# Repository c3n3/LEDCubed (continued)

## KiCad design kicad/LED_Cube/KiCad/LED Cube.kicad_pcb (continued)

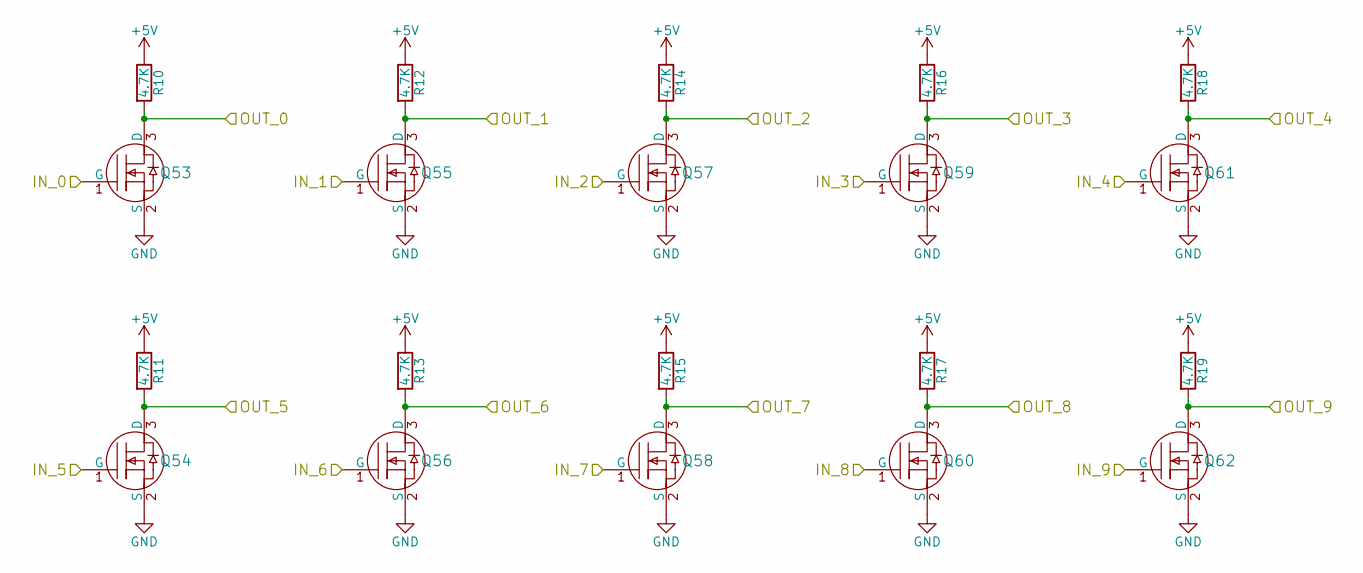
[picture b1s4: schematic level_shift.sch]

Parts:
Q53, Q54, Q55, Q56, Q57, Q58, Q59, Q60, Q61, Q62: N-Channel_MOSFET; SOT-23
R10, R11, R12, R13, R14, R15, R16, R17, R18, R19: 4.7K; R_0805_HandSoldering

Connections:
+5V: R10.1, R11.1, R12.1, R13.1, R14.1, R15.1, R16.1, R17.1, R18.1, R19.1; also elsewhere on the board
/Level Shift/IN_0: Q53.1 (G); also elsewhere on the board
/Level Shift/IN_1: Q55.1 (G); also elsewhere on the board
/Level Shift/IN_2: Q57.1 (G); also elsewhere on the board
/Level Shift/IN_3: Q59.1 (G); also elsewhere on the board
/Level Shift/IN_4: Q61.1 (G); also elsewhere on the board
/Level Shift/IN_5: Q54.1 (G); also elsewhere on the board
/Level Shift/IN_6: Q56.1 (G); also elsewhere on the board
/Level Shift/IN_7: Q58.1 (G); also elsewhere on the board
/Level Shift/IN_8: Q60.1 (G); also elsewhere on the board
/Level Shift/IN_9: Q62.1 (G); also elsewhere on the board
/Level Shift/OUT_0: Q53.3 (D), R10.2; also elsewhere on the board
/Level Shift/OUT_1: Q55.3 (D), R12.2; also elsewhere on the board
/Level Shift/OUT_2: Q57.3 (D), R14.2; also elsewhere on the board
/Level Shift/OUT_3: Q59.3 (D), R16.2; also elsewhere on the board
/MOSFET_TREE/C_B: Q62.3 (D), R19.2; also elsewhere on the board
/MOSFET_TREE/C_G: Q60.3 (D), R17.2; also elsewhere on the board
/MOSFET_TREE/C_R: Q58.3 (D), R15.2; also elsewhere on the board
/MOSFET_TREE/L_0: Q61.3 (D), R18.2; also elsewhere on the board
/MOSFET_TREE/L_1: Q54.3 (D), R11.2; also elsewhere on the board
/MOSFET_TREE/L_2: Q56.3 (D), R13.2; also elsewhere on the board
GND: Q53.2 (S), Q54.2 (S), Q55.2 (S), Q56.2 (S), Q57.2 (S), Q58.2 (S), Q59.2 (S), Q60.2 (S), Q61.2 (S), Q62.2 (S); also elsewhere on the board

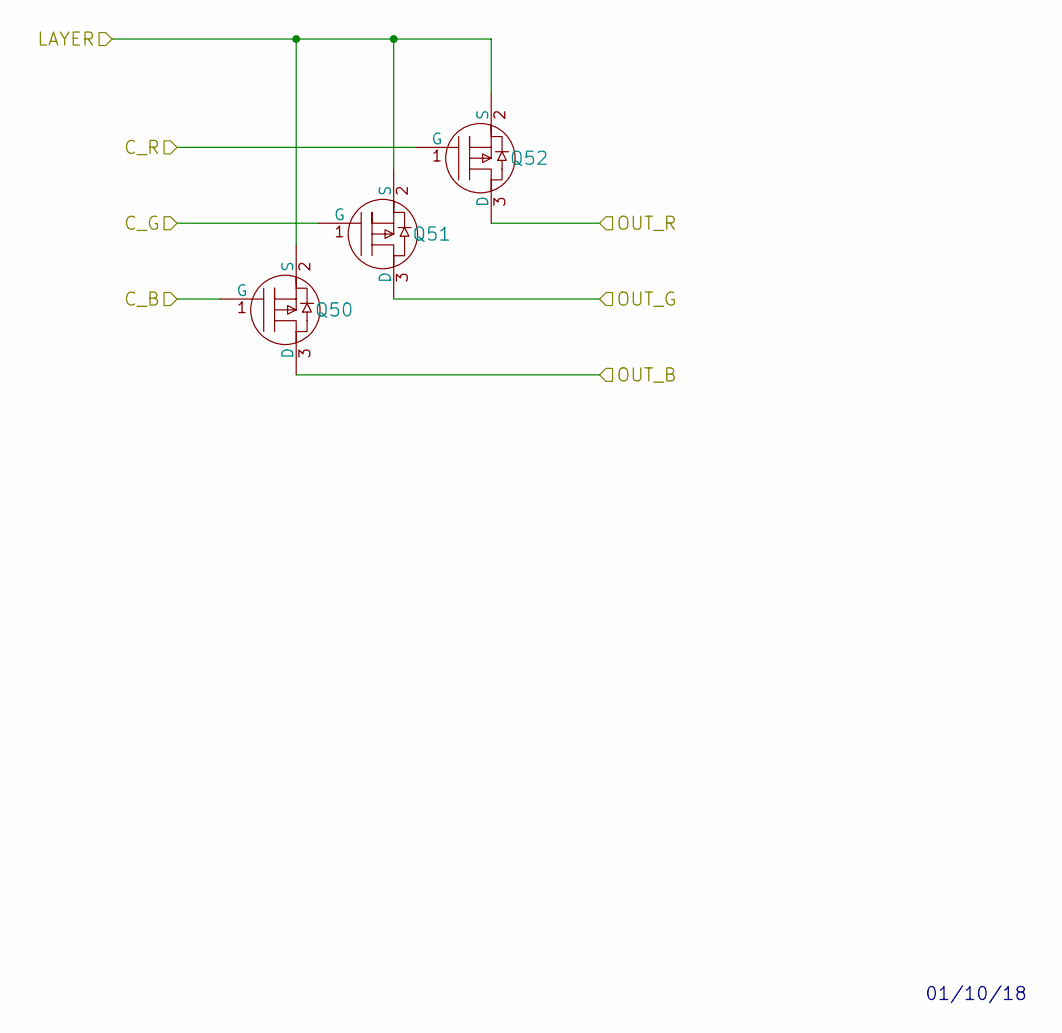
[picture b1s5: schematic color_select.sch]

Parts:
Q17, Q18, Q19: P-Channel_MOSFET; SOT-23

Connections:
/MOSFET_TREE/C_B: Q17.1 (G); also elsewhere on the board
/MOSFET_TREE/C_G: Q18.1 (G); also elsewhere on the board
/MOSFET_TREE/C_R: Q19.1 (G); also elsewhere on the board
/MOSFET_TREE/Color_Select_00/LAYER: Q17.2 (S), Q18.2 (S), Q19.2 (S); also elsewhere on the board
/MOSFET_TREE/L_00_B: Q17.3 (D); also elsewhere on the board
/MOSFET_TREE/L_00_G: Q18.3 (D); also elsewhere on the board
/MOSFET_TREE/L_00_R: Q19.3 (D); also elsewhere on the board

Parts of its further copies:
Q20, Q21, Q22, Q23, Q24, Q25, Q26, Q27, Q28, Q29, Q30, Q31, Q32, Q33, Q34, Q35, Q36, Q37, Q38, Q39, Q40, Q41, Q42, Q43, Q44, Q45, Q46, Q47, Q48, Q49, Q50, Q51, Q52: P-Channel_MOSFET; SOT-23

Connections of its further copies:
/MOSFET_TREE/C_B: Q20.1 (G), Q23.1 (G), Q26.1 (G), Q29.1 (G), Q32.1 (G), Q35.1 (G), Q38.1 (G), Q41.1 (G), Q44.1 (G), Q47.1 (G), Q50.1 (G); also elsewhere on the board
/MOSFET_TREE/C_G: Q21.1 (G), Q24.1 (G), Q27.1 (G), Q30.1 (G), Q33.1 (G), Q36.1 (G), Q39.1 (G), Q42.1 (G), Q45.1 (G), Q48.1 (G), Q51.1 (G); also elsewhere on the board
/MOSFET_TREE/C_R: Q22.1 (G), Q25.1 (G), Q28.1 (G), Q31.1 (G), Q34.1 (G), Q37.1 (G), Q40.1 (G), Q43.1 (G), Q46.1 (G), Q49.1 (G), Q52.1 (G); also elsewhere on the board
/MOSFET_TREE/Color_Select_01/LAYER: Q20.2 (S), Q21.2 (S), Q22.2 (S); also elsewhere on the board
/MOSFET_TREE/Color_Select_02/LAYER: Q23.2 (S), Q24.2 (S), Q25.2 (S); also elsewhere on the board
/MOSFET_TREE/Color_Select_03/LAYER: Q26.2 (S), Q27.2 (S), Q28.2 (S); also elsewhere on the board
/MOSFET_TREE/Color_Select_04/LAYER: Q29.2 (S), Q30.2 (S), Q31.2 (S); also elsewhere on the board
/MOSFET_TREE/Color_Select_05/LAYER: Q32.2 (S), Q33.2 (S), Q34.2 (S); also elsewhere on the board
/MOSFET_TREE/Color_Select_06/LAYER: Q35.2 (S), Q36.2 (S), Q37.2 (S); also elsewhere on the board
/MOSFET_TREE/Color_Select_07/LAYER: Q38.2 (S), Q39.2 (S), Q40.2 (S); also elsewhere on the board
/MOSFET_TREE/Color_Select_08/LAYER: Q41.2 (S), Q42.2 (S), Q43.2 (S); also elsewhere on the board
/MOSFET_TREE/Color_Select_09/LAYER: Q44.2 (S), Q45.2 (S), Q46.2 (S); also elsewhere on the board
/MOSFET_TREE/Color_Select_10/LAYER: Q47.2 (S), Q48.2 (S), Q49.2 (S); also elsewhere on the board
/MOSFET_TREE/Color_Select_11/LAYER: Q50.2 (S), Q51.2 (S), Q52.2 (S); also elsewhere on the board
/MOSFET_TREE/L_01_B: Q20.3 (D); also elsewhere on the board
/MOSFET_TREE/L_01_G: Q21.3 (D); also elsewhere on the board
/MOSFET_TREE/L_01_R: Q22.3 (D); also elsewhere on the board
/MOSFET_TREE/L_02_B: Q23.3 (D); also elsewhere on the board
/MOSFET_TREE/L_02_G: Q24.3 (D); also elsewhere on the board
/MOSFET_TREE/L_02_R: Q25.3 (D); also elsewhere on the board
/MOSFET_TREE/L_03_B: Q26.3 (D); also elsewhere on the board
/MOSFET_TREE/L_03_G: Q27.3 (D); also elsewhere on the board
/MOSFET_TREE/L_03_R: Q28.3 (D); also elsewhere on the board
/MOSFET_TREE/L_04_B: Q29.3 (D); also elsewhere on the board
/MOSFET_TREE/L_04_G: Q30.3 (D); also elsewhere on the board
/MOSFET_TREE/L_04_R: Q31.3 (D); also elsewhere on the board
/MOSFET_TREE/L_05_B: Q32.3 (D); also elsewhere on the board
/MOSFET_TREE/L_05_G: Q33.3 (D); also elsewhere on the board
/MOSFET_TREE/L_05_R: Q34.3 (D); also elsewhere on the board
/MOSFET_TREE/L_06_B: Q35.3 (D); also elsewhere on the board
/MOSFET_TREE/L_06_G: Q36.3 (D); also elsewhere on the board
/MOSFET_TREE/L_06_R: Q37.3 (D); also elsewhere on the board
/MOSFET_TREE/L_07_B: Q38.3 (D); also elsewhere on the board
/MOSFET_TREE/L_07_G: Q39.3 (D); also elsewhere on the board
/MOSFET_TREE/L_07_R: Q40.3 (D); also elsewhere on the board
/MOSFET_TREE/L_08_B: Q41.3 (D); also elsewhere on the board
/MOSFET_TREE/L_08_G: Q42.3 (D); also elsewhere on the board
/MOSFET_TREE/L_08_R: Q43.3 (D); also elsewhere on the board
/MOSFET_TREE/L_09_B: Q44.3 (D); also elsewhere on the board
/MOSFET_TREE/L_09_G: Q45.3 (D); also elsewhere on the board
/MOSFET_TREE/L_09_R: Q46.3 (D); also elsewhere on the board
/MOSFET_TREE/L_10_B: Q47.3 (D); also elsewhere on the board
/MOSFET_TREE/L_10_G: Q48.3 (D); also elsewhere on the board
/MOSFET_TREE/L_10_R: Q49.3 (D); also elsewhere on the board
/MOSFET_TREE/L_11_B: Q50.3 (D); also elsewhere on the board
/MOSFET_TREE/L_11_G: Q51.3 (D); also elsewhere on the board
/MOSFET_TREE/L_11_R: Q52.3 (D); also elsewhere on the board

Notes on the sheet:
01/10/18

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
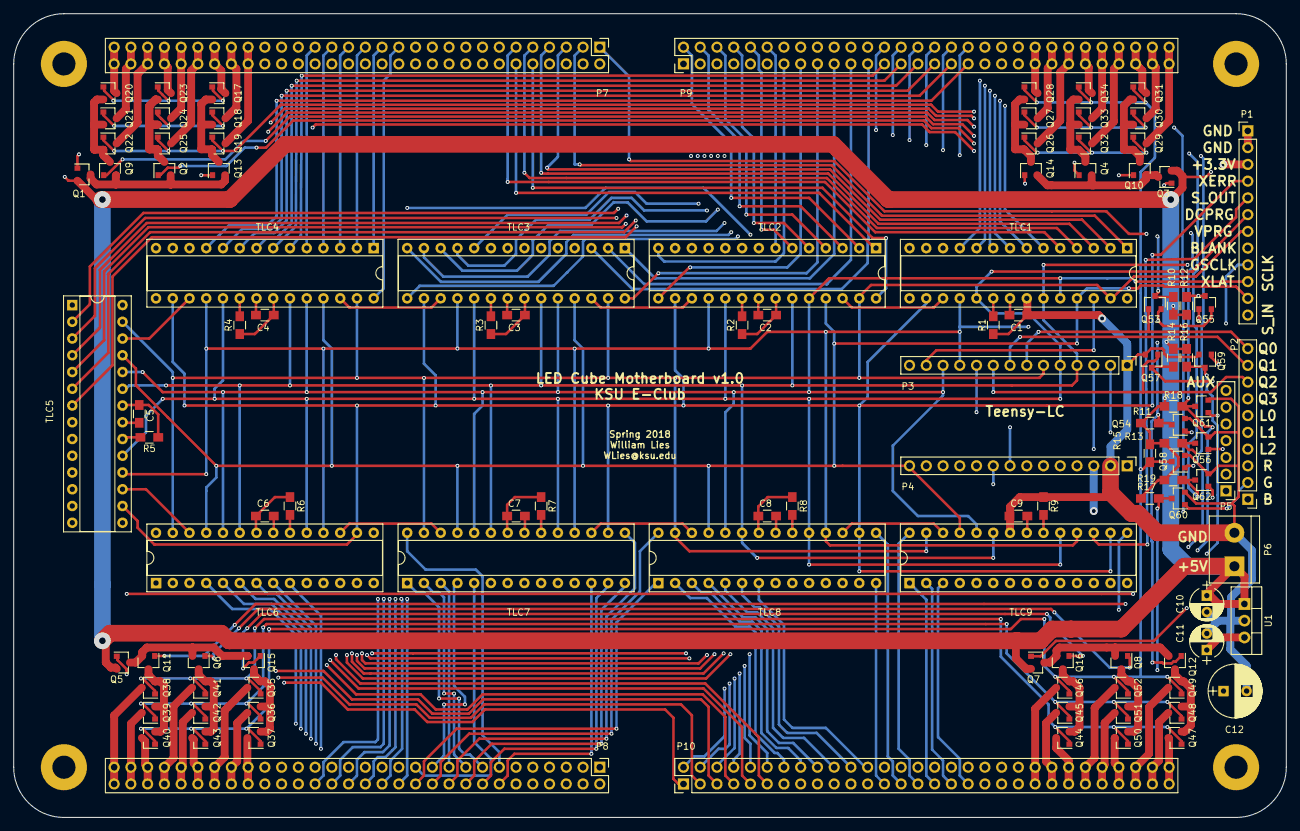
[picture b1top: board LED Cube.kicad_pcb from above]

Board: 4 copper layers, 193.0 x 121.9 mm, 113 parts (0 on the bottom side), 252 nets.

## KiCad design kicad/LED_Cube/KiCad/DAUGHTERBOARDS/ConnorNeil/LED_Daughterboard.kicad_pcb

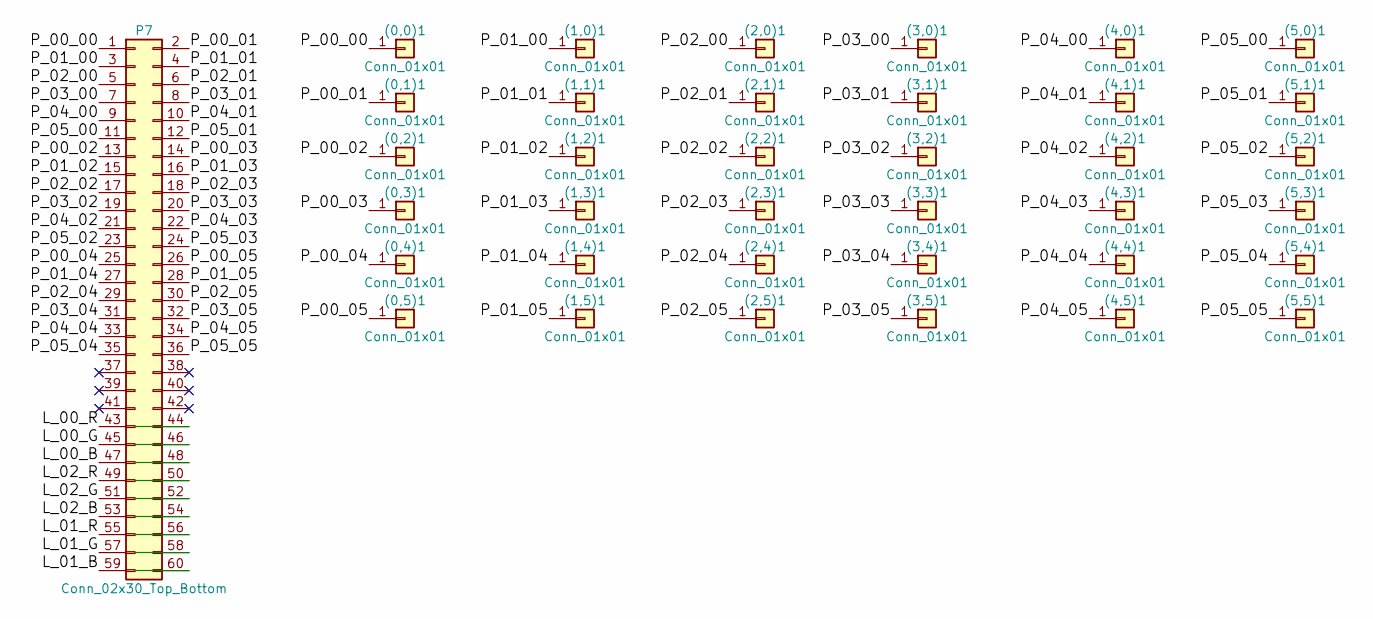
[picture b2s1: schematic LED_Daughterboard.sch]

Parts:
(0,0)1, (0,1)1, (0,2)1, (0,3)1, (0,4)1, (0,5)1, (1,0)1, (1,1)1, (1,2)1, (1,3)1, (1,4)1, (1,5)1, (2,0)1, (2,1)1, (2,2)1, (2,3)1, (2,4)1, (2,5)1, (3,0)1, (3,1)1, (3,2)1, (3,3)1, (3,4)1, (3,5)1, (4,0)1, (4,1)1, (4,2)1, (4,3)1, (4,4)1, (4,5)1, (5,0)1, (5,1)1, (5,2)1, (5,3)1, (5,4)1, (5,5)1: Conn_01x01; Pin_Header_Straight_1x01_Pitch2.54mm
P7: Conn_02x30_Top_Bottom; Pin_Header_Straight_2x30_Pitch2.54mm

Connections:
/L_00_B: P7.47
/L_00_G: P7.45
/L_00_R: P7.43
/L_01_B: P7.59
/L_01_G: P7.57
/L_01_R: P7.55
/L_02_B: P7.53
/L_02_G: P7.51
/L_02_R: P7.49
/P_00_00: (0,0)1.1, P7.1
/P_00_01: (0,1)1.1, P7.2
/P_00_02: (0,2)1.1, P7.13
/P_00_03: (0,3)1.1, P7.14
/P_00_04: (0,4)1.1, P7.25
/P_00_05: (0,5)1.1, P7.26
/P_01_00: (1,0)1.1, P7.3
/P_01_01: (1,1)1.1, P7.4
/P_01_02: (1,2)1.1, P7.15
/P_01_03: (1,3)1.1, P7.16
/P_01_04: (1,4)1.1, P7.27
/P_01_05: (1,5)1.1, P7.28
/P_02_00: (2,0)1.1, P7.5
/P_02_01: (2,1)1.1, P7.6
/P_02_02: (2,2)1.1, P7.17
/P_02_03: (2,3)1.1, P7.18
/P_02_04: (2,4)1.1, P7.29
/P_02_05: (2,5)1.1, P7.30
/P_03_00: (3,0)1.1, P7.7
/P_03_01: (3,1)1.1, P7.8
/P_03_02: (3,2)1.1, P7.19
/P_03_03: (3,3)1.1, P7.20
/P_03_04: (3,4)1.1, P7.31
/P_03_05: (3,5)1.1, P7.32
/P_04_00: (4,0)1.1, P7.9
/P_04_01: (4,1)1.1, P7.10
/P_04_02: (4,2)1.1, P7.21
/P_04_03: (4,3)1.1, P7.22
/P_04_04: (4,4)1.1, P7.33
/P_04_05: (4,5)1.1, P7.34
/P_05_00: (5,0)1.1, P7.11
/P_05_01: (5,1)1.1, P7.12
/P_05_02: (5,2)1.1, P7.23
/P_05_03: (5,3)1.1, P7.24
/P_05_04: (5,4)1.1, P7.35
/P_05_05: (5,5)1.1, P7.36

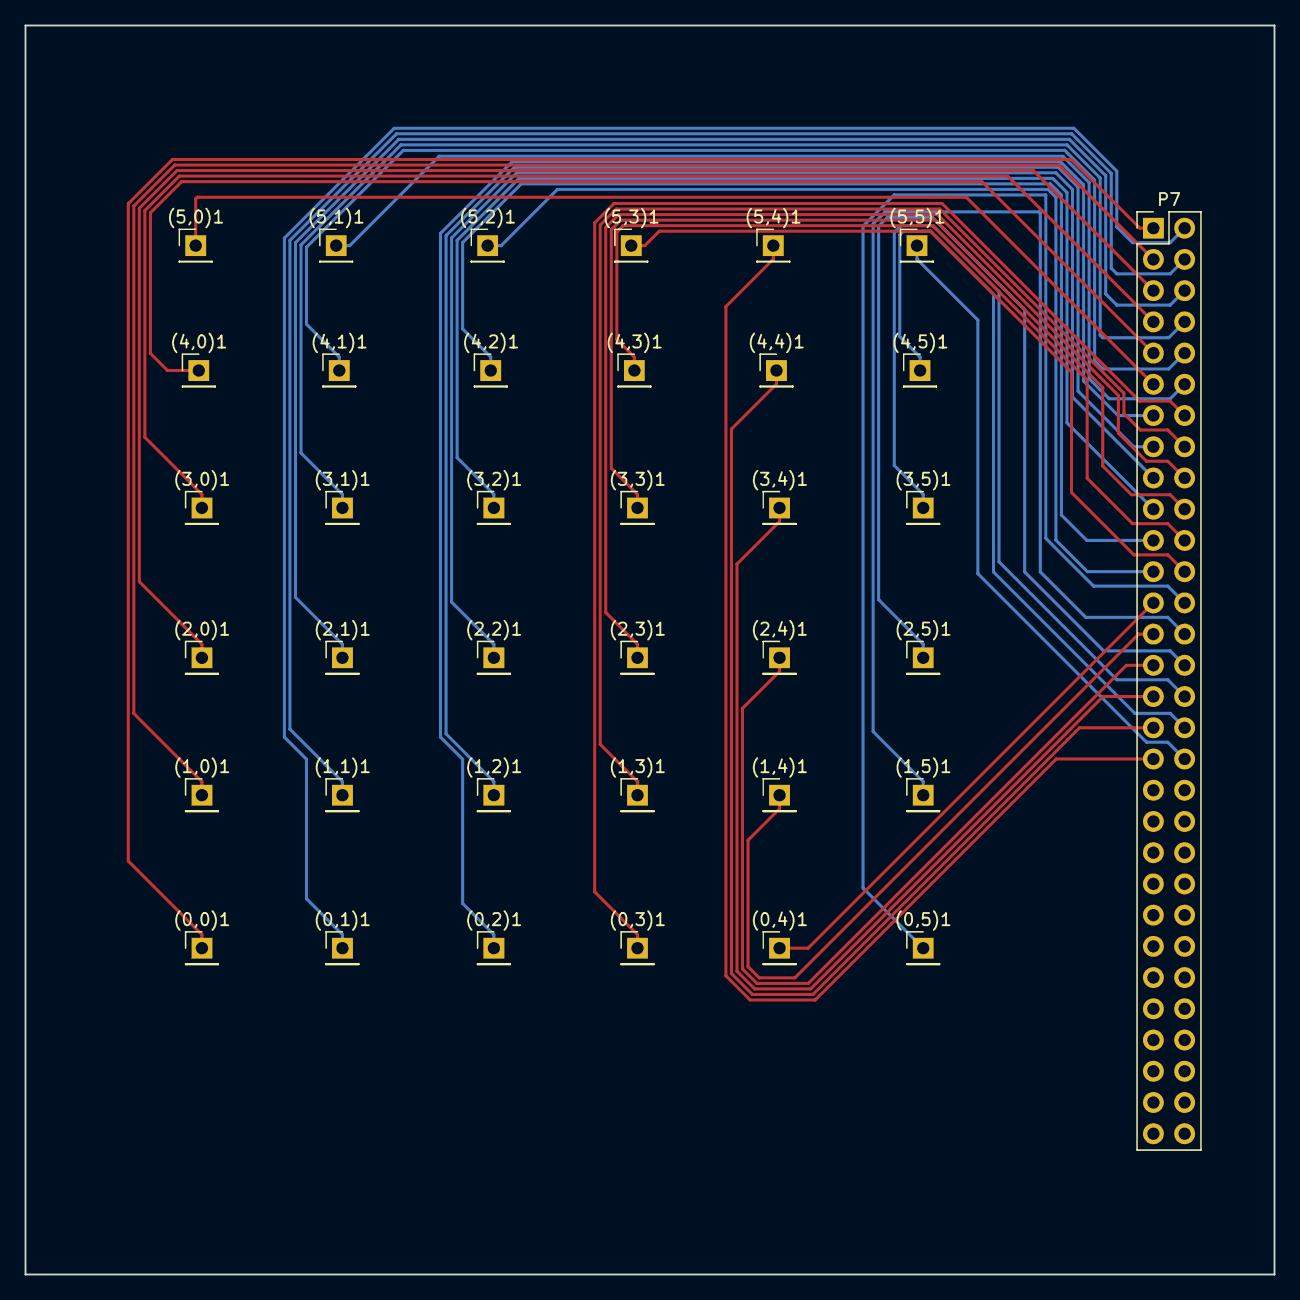
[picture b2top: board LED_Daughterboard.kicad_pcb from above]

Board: 2 copper layers, 101.6 x 101.6 mm, 37 parts (0 on the bottom side), 36 nets.

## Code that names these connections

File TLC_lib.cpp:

//
// TLC_lib.cpp
// C++ code
// ----------------------------------
// Developed with embedXcode
// http://embedXcode.weebly.com
//
// Project 		TeensyTest
//
// Created by 	William Lies, 10/21/17 9:56 AM
// 				William Lies
//
// Copyright 	(c) William Lies, 2017
// Licence		licence
//
// See 			TLC_lib.h and ReadMe.txt for references
//


/*------------------------------------------------------
 *  Automatic Includes
 -----------------------------------------------------*/
// Core library for code-sense - IDE-based
#if defined(TEENSYDUINO) // Teensy specific
#include "Arduino.h"
#else // error
#error Platform not defined
#endif // end IDE

/*------------------------------------------------------
 *  User Includes
 -----------------------------------------------------*/
#include "TLC_lib.h"
#include "SPI.h"
#include "MUX_lib.h"

/*------------------------------------------------------
 *  Static Variables
 -----------------------------------------------------*/
//static uint8_t gs_buf[NUM_BYTES];  //buffer for greyscale

/*------------------------------------------------------
 *  Funciton Definitions
 -----------------------------------------------------*/

//Initializes pins and buffer for TLC
//Must be called before any other functions in this file.
//
void init_TLC(){
    pinMode( BLANK, OUTPUT);    //BLANK
    pinMode( GCLK, OUTPUT);    //GCLK
    pinMode( XLAT, OUTPUT);    //XLAT
    pinMode( MOSI, OUTPUT);    //SIN (MOSI)
    pinMode( SCK,  OUTPUT);    //SCK
    pinMode( VPRG, OUTPUT);
    pinMode( DCPRG, OUTPUT);
    
    digitalWriteFast( BLANK, HIGH   );    //BLANK
    digitalWriteFast( GCLK, LOW     );    //GCLK
    digitalWriteFast( XLAT, LOW     );    //XLAT
    digitalWriteFast( MOSI, LOW     );    //SIN (MOSI)
    digitalWriteFast( SCK,  LOW     );    //SCK
    digitalWriteFast( VPRG, HIGH);
    digitalWriteFast( DCPRG, LOW);
    
    digitalWriteFast( BLANK, LOW);      //Blank falling edge
    //SPI.usingInterrupt(TIMER0_COMPA_vect);
    SPI.begin();
    SPI.beginTransaction(SPISettings(SCLK_FREQ, MSBFIRST, SPI_MODE0));
    pinMode( MISO, INPUT);
    digitalWriteFast( MISO, HIGH);//Internal pullup on MISO
    
    analogWriteFrequency(GCLK, PWM_FREQ); // All PWM pins on FTM0 change
    /* Hello. Be careful with this pwm frequency. It needs to be much higher (4096 x) than the "refresh rate" of the
     LEDs, or else they will be very flickery.
     */
    analogWrite(GCLK, 128);
}



// Writes Dot Correction value to the chip (0xFF)
// Call once after startup
//
void write_dot_correction(uint8_t * buf){
    digitalWriteFast(VPRG, HIGH);
    digitalWriteFast(DCPRG, HIGH);
    
    //SPI.beginTransaction(SPISettings(SCLK_FREQ, MSBFIRST, SPI_MODE0));
    SPI.transfer((uint8_t *)buf, NUM_BYTES);
    //SPI.endTransaction();
    
    digitalWriteFast(XLAT, HIGH);   //XLAT Pulse
    delayMicroseconds(10);
    digitalWriteFast(XLAT, LOW);
    delayMicroseconds(10);
    digitalWriteFast(VPRG, LOW);
}



// Writes Grey Scale buffer to the chip
// Call to update TLC chain
//
void write_grey_scale(uint8_t * buf){
    //analogWrite(GCLK, 0);
    ///digitalWriteFast(BLANK, HIGH);
    ///digitalWriteFast(BLANK, LOW);
    
    //SPI.beginTransaction(SPISettings(SCLK_FREQ, MSBFIRST, SPI_MODE0));
    SPI.transfer((uint8_t *)buf, NUM_BYTES);
    //SPI.endTransaction();
    
    digitalWriteFast(XLAT, HIGH);   //XLAT Pulse
    digitalWriteFast(XLAT, LOW);
    
    digitalWriteFast(BLANK, HIGH);
    digitalWriteFast(BLANK, LOW);
    //digitalWriteFast(BLANK, LOW);
    //analogWrite(GCLK, 128);
}


// Modifies the buffer (buf) such that the TLC channel (chn) will have the indicated value (val)
// 0 <= chn < NUM_CHNL
// 0 <= val < 4096 (12 bits)
// buf is a pointer to the buffer (layer?) you want to modify.
// NOTE: TLC clocks data in MSB first.
void set_channel( uint8_t chn, uint16_t val, uint8_t* buf ){
    chn = NUM_CHNL-chn-1;   //The data is clocked out ch 15 first. Do this so channel numbers match datasheet.
    buf += (chn / 2) * 3; //move pointer up (every 2 channels is 3 full bytes)
    val &= 0x0FFF;        //mask off upper four bits
    
    if( chn % 2 ){  //if channel is odd (write half byte then full byte
        buf[1] &= 0xF0;         //set lower half of split byte to 0
        buf[1] |= (uint8_t)(val >> 8);   //put upper 4 bits of val into target byte
        buf[2] =  (uint8_t)val; //put lower 8 bits of val into target byte
        /*buf[1] &= 0xF0;
        buf[2] = 0;*/
    }
    else{           //if channel is even (write full byte then half byte
        buf[0] = (uint8_t)(val >> 4);  //put upper 8 bits in
        buf[1] &= 0x0F;         //set upper half of split byte to zero
        buf[1] |= (uint8_t)((val & 0x000F) << 4);   //put in lower 4 bits of val into upper half of target byte
    }
}

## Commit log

2019-03-19 Add files via upload
    These are the base files
2019-03-21 cleanUp
    fileCleanUp
2019-03-21 Layout
    Layout is basically done, mainSwitch still needs alot of work
2019-03-21 not much
    not much
2019-03-21 not much again
    same
2019-03-22 scac
    dsfsdgsw
2019-03-25 idk
    something
2019-04-03 snake
    sanek
2019-04-03 aa
    aa
2019-05-05 stuff
    stuff
2019-05-10 mADE SNAKE
    YESS
2019-05-12 Added Stuff, mainly start of pong
2019-06-05 Update TeensyTest.ino
    Addded start of pong
2019-08-24 Revert back to github from bitbucket
2019-08-30 Fixed some things and other stuff
2019-09-11 Cleaned snake
2019-09-20 Last Commit before version control really kicks in
2019-09-20 Set theme jekyll-theme-hacker
2019-09-22 Added multiple files to the sketch to house different parts of the program (have not tested with cube)
2019-09-23 Made multi file work and drawing chars work too
2019-09-27 Created Branch
2019-10-02 test file
2019-10-05 This allows us to nt have to worry about the length of the app functions pointer array
2020-06-05 This is a commit to which I am not sure the imlications
2020-06-08 This is a major restructor of the entire system. This is also during a time in which I could not test the code with the actual cube. I do not claim it works; I do claim it compiles
2020-06-08 Deleted an unwanted file
2020-06-16 This is another large commit that has made lots of things pretty and added a whole bunch of stuff Also made sure all .h files were properly commented
2020-06-16 made the readme a glorious document, give me a pultzer prize already
2020-07-10 This adds the kicad files, and adds relativistic to the tools
2020-07-16 This adds minesweeper and makes the vector class a template
2020-12-13 Added stuff
2022-02-28 Did more
